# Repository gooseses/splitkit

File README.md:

Files for my custom ergo split keyboard 

Made with Ergogen and ZMK

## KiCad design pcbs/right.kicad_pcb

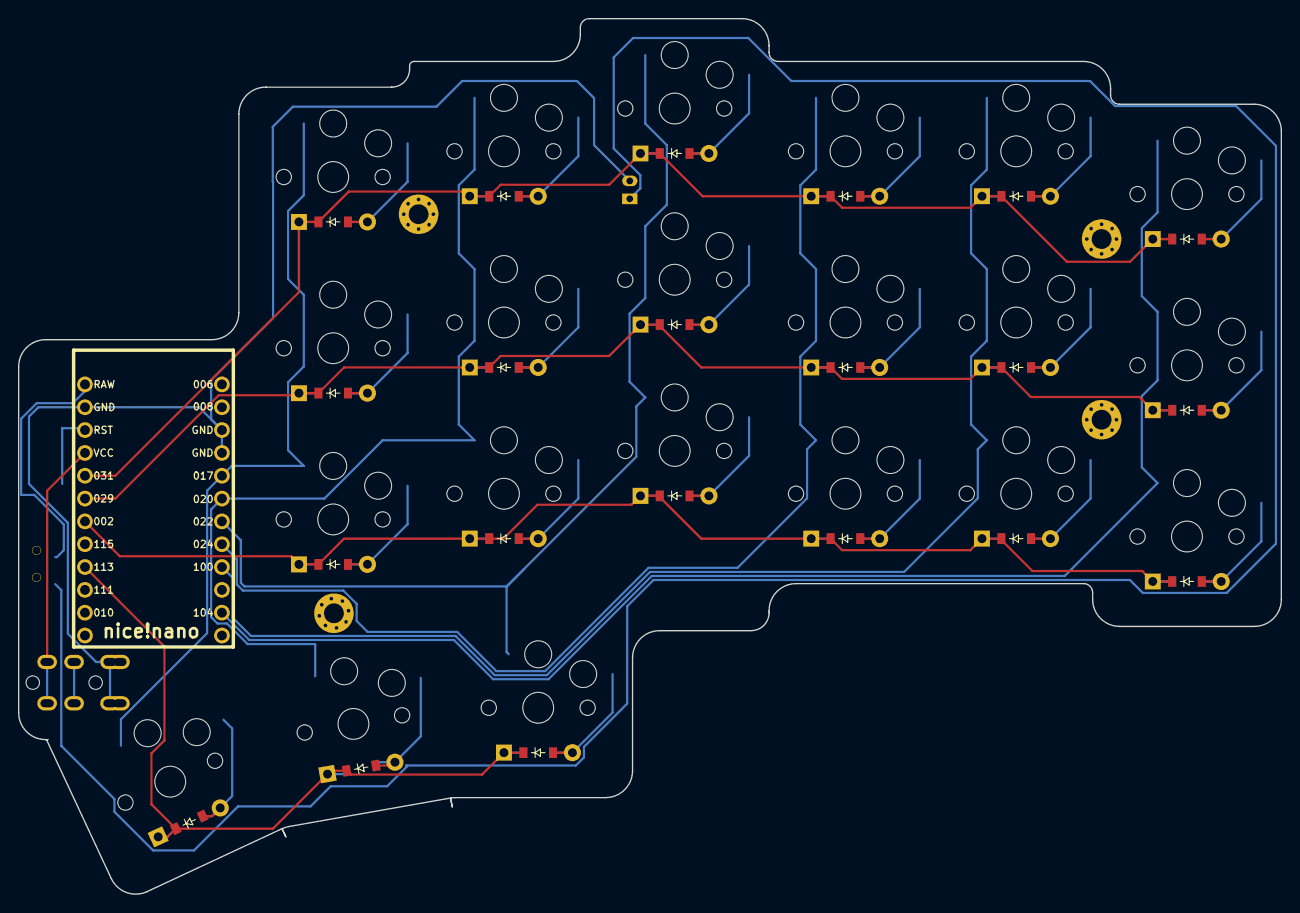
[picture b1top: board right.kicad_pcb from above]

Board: 2 copper layers, 140.5 x 97.4 mm, 51 parts (0 on the bottom side), 36 nets.

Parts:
B1: SW_TACT_ALPS_SKQGABE010
D1, D2, D3, D4, D5, D6, D7, D8, D9, D10, D11, D12, D13, D14, D15, D16, D17, D18, D19, D20, D21: ComboDiode
JST1: JST_PH_S2B-PH-K_02x2.00mm_Angled
MCU1: nice_nano
S1, S2, S3, S4, S5, S6, S7, S8, S9, S10, S11, S12, S13, S14, S15, S16, S17, S18, S19, S20, S21: PG1350
T1: SPDT_C128955
TRRS1: TRRS-PJ-320A-dual
_1, _2, _3, _4: MountingHole_2.2mm_M2_Pad_Via

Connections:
GND: B1.1, JST1.2, MCU1.3, MCU1.4, MCU1.23, TRRS1.1, TRRS1.2
P002: D4.1, D7.1, D10.1, D13.1, D16.1, D19.1, MCU1.18
P017: MCU1.5, S1.1, S19.1, S20.1, S21.1
P020: MCU1.6, S2.1, S16.1, S17.1, S18.1
P022: MCU1.7, S3.1, S13.1, S14.1, S15.1
P024: MCU1.8, S10.1, S11.1, S12.1
P029: D5.1, D8.1, D11.1, D14.1, D17.1, D20.1, MCU1.19
P031: D6.1, D9.1, D12.1, D15.1, D18.1, D21.1, MCU1.20
P100: MCU1.9, S7.1, S8.1, S9.1
P104: MCU1.11, S4.1, S5.1, S6.1
P113: D1.1, D2.1, D3.1, MCU1.16
RAW: MCU1.24, T1.2
RST: B1.2, MCU1.22
VCC: MCU1.21, TRRS1.4
mirror_index_bottom: D16.2, S16.2
mirror_index_home: D17.2, S17.2
mirror_index_top: D18.2, S18.2
mirror_inner_bottom: D19.2, S19.2
mirror_inner_home: D20.2, S20.2
mirror_inner_top: D21.2, S21.2
mirror_middle_bottom: D13.2, S13.2
mirror_middle_home: D14.2, S14.2
mirror_middle_top: D15.2, S15.2
mirror_outer_bottom: D4.2, S4.2
mirror_outer_home: D5.2, S5.2
mirror_outer_top: D6.2, S6.2
mirror_pinky_bottom: D7.2, S7.2
mirror_pinky_home: D8.2, S8.2
mirror_pinky_top: D9.2, S9.2
mirror_reachy_cluster: D1.2, S1.2
mirror_ring_bottom: D10.2, S10.2
mirror_ring_home: D11.2, S11.2
mirror_ring_top: D12.2, S12.2
mirror_stim_cluster: D3.2, S3.2
mirror_tucky_cluster: D2.2, S2.2
pos: JST1.1, T1.1

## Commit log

2024-08-18 init
2024-10-26 Initial User Config.
2024-10-26 kHAWWGKL
2024-10-26 splitkit
2024-10-27 fixed firmware
2024-10-27 actually fixed
2024-10-27 bottom row fix
2024-11-25 fix again
2024-11-25 try again
2024-11-25 tAHAH
2024-11-25 PLEASE
2024-11-25 test
2024-11-25 again
2024-11-25 tryagain
2024-11-25 try agian
2024-11-25 lkjfdl
2024-11-25 AWJKFHKJ
2024-11-25 opps
